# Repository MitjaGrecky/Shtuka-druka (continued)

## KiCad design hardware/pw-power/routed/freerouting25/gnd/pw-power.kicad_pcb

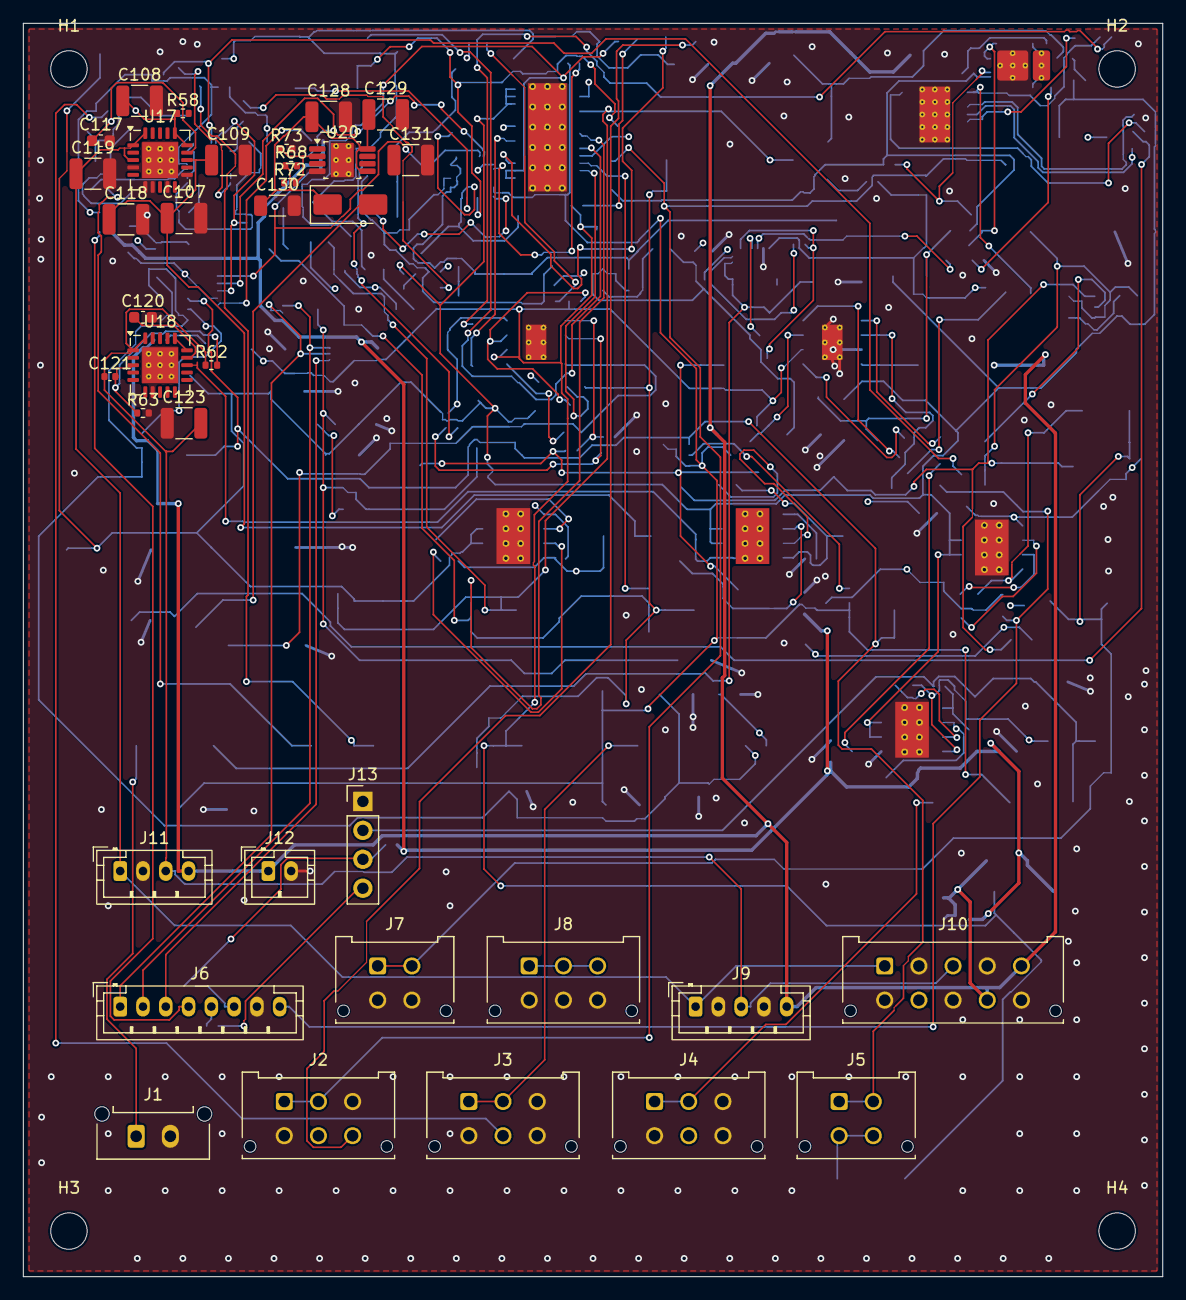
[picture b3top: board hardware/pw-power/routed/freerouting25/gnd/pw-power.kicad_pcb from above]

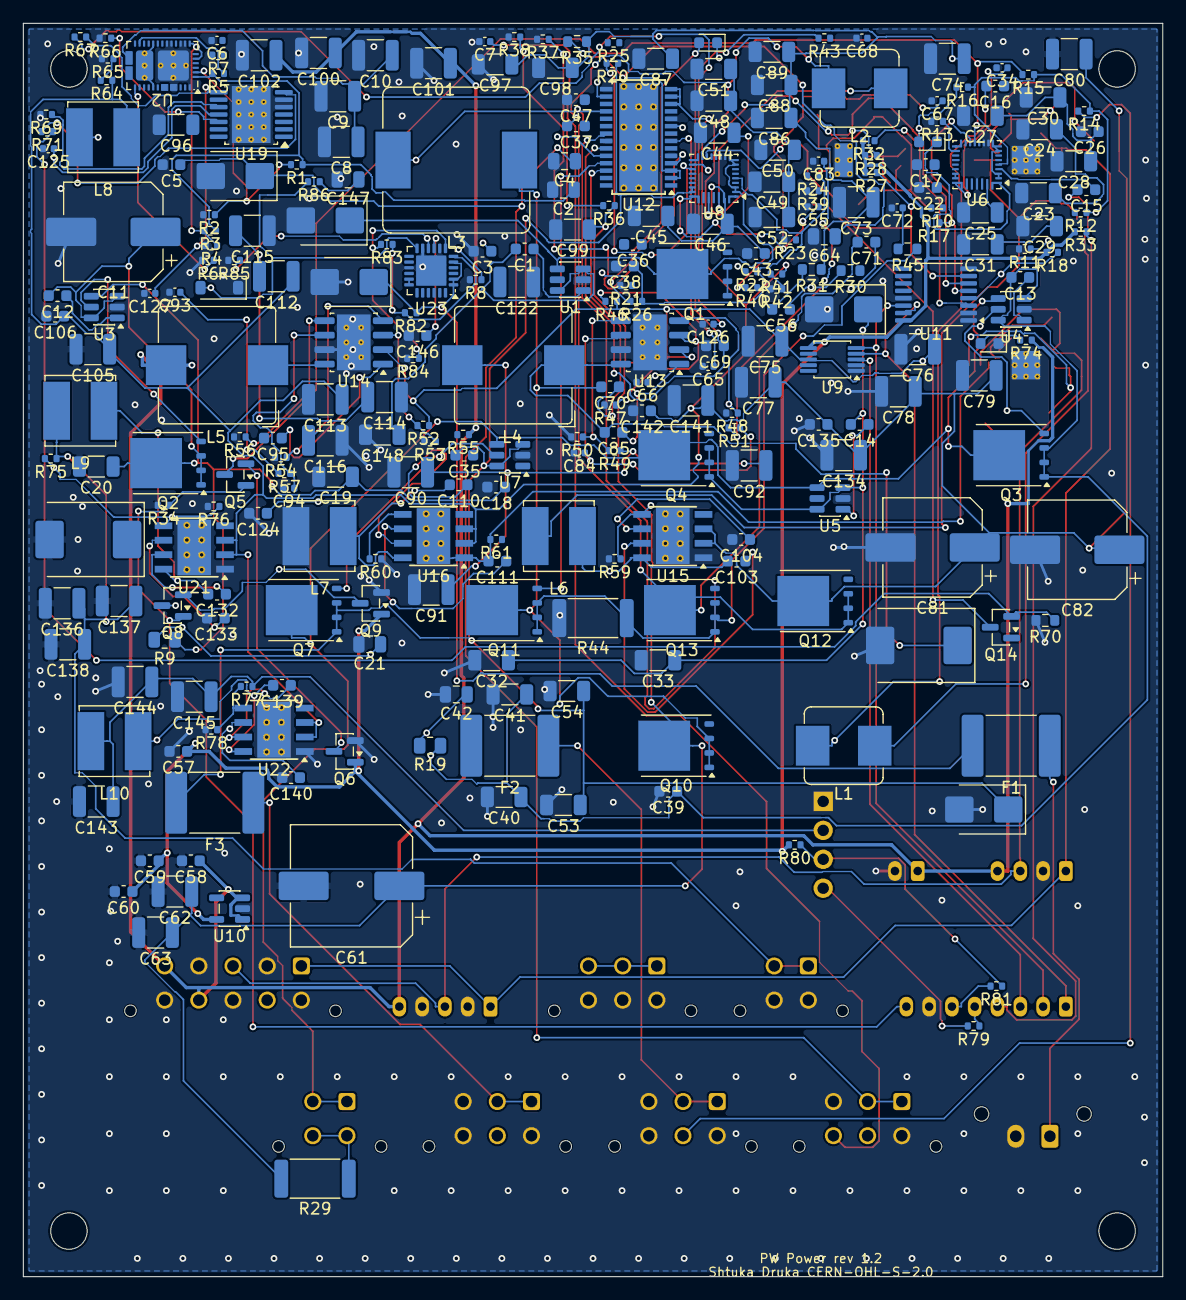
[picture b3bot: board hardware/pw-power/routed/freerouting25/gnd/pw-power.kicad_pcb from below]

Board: 4 copper layers, 100.0 x 110.0 mm, 313 parts (273 on the bottom side), 169 nets.

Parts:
C1, C12, C13, C14, C26, C35, C47, C85, C95, C103, C110, C132, C139: 100n 25V; C_0603_1608Metric
C2: 10u; C_0805_2012Metric
C3: 4.7u; C_0603_1608Metric
C4: 4.7u 25V; C_0805_2012Metric
C5, C146: 10n 50V; C_0603_1608Metric
C6, C7: 330p; C_0402_1005Metric
C8, C9, C107, C108, C109, C114, C115, C116, C136, C137, C138, C143, C144, C145: 22u 25V; C_1210_3225Metric
C10, C118, C119, C122: 10u 25V; C_1210_3225Metric
C11: 47u 35V; CP_Elec_8x10.5
C15, C16, C36, C37: 47n 25V; C_0603_1608Metric
C17, C38: 4.7u 10V; C_0603_1608Metric
C18, C22, C39, C43, C56, C70, C71: 100n 50V; C_0603_1608Metric
C19, C20, C23, C24, C25, C40, C41, C44, C45, C46, C148: 10u 35V; C_1206_3216Metric
C21, C42: 2.2u 35V; C_0805_2012Metric
C27, C28, C29, C30, C31, C32, C33, C48, C49, C50, C51, C52, C53, C54: 10u 25V; C_1206_3216Metric
C34, C55: 1n 50V; C_0402_1005Metric
C57, C60: 100n; C_0603_1608Metric
C58, C59, C104, C111, C117, C120, C133, C140: 1u; C_0603_1608Metric
C61: 100u 35V; CP_Elec_10x10.5
C62, C63, C105, C112, C113, C134, C141: 10u 50V; C_1210_3225Metric
C64, C147: 1u 50V; C_0805_2012Metric
C65: 220p; C_0402_1005Metric
C66: 100n; C_0402_1005Metric
C67: 33n; C_0402_1005Metric
C68: 560p; C_0402_1005Metric
C69, C124: 1u 25V; C_0603_1608Metric
C72, C84, C94: 47p; C_0402_1005Metric
C73, C74, C75, C76: 4.7u 50V; C_1210_3225Metric
C77, C78, C79, C80: 10u 35V; C_1210_3225Metric
C81, C82: 100u 35V; CP_Elec_8x10.5
C83, C93: 4.7n; C_0402_1005Metric
C86, C87, C88, C89, C96, C97, C98, C99: 2.2u 50V; C_1206_3216Metric
C90, C91, C92, C100, C101, C102: 47u 10V; C_1210_3225Metric
C106, C135, C142: 220n 50V; C_0603_1608Metric
C121: 10n; C_0402_1005Metric
C123: 47u 25V; C_1210_3225Metric
C125: 47n; C_0402_1005Metric
C126: 22n; C_0402_1005Metric
C127: 470p; C_0402_1005Metric
C128, C129, C131: 4.7u 100V; C_1210_3225Metric
C130: 1u 100V; C_1206_3216Metric
D1: SMBJ28CA; D_SMB
D2, D3: SMBJ20CA; D_SMB
D4, D6: SMBJ13CA; D_SMB
D5, D7, D11: green; LED_0603_1608Metric
D8, D9: B560C; D_SMC
D10: SS1H10; D_SMA
D12: BZT52C3V3; D_SOD-123
F1: 5A; Fuse_2920_7451Metric
F2, F3: 10A; Fuse_2920_7451Metric
H1, H2, H3, H4: M3; MountingHole_3.2mm_M3_ISO7380
J1: DC in; Molex_Micro-Fit_3.0_43650-0215_1x02_P3.00mm_Vertical
J2: USB-C Power in; Molex_Micro-Fit_3.0_43045-0612_2x03_P3.00mm_Vertical
J3: Battery 1; Molex_Micro-Fit_3.0_43045-0612_2x03_P3.00mm_Vertical
J4: Battery 2; Molex_Micro-Fit_3.0_43045-0612_2x03_P3.00mm_Vertical
J5: On/Off switch; Molex_Micro-Fit_3.0_43045-0412_2x02_P3.00mm_Vertical
J6: Power telemetry to P2; JST_PH_B8B-PH-K_1x08_P2.00mm_Vertical
J7: 15 V to H5; Molex_Micro-Fit_3.0_43045-0412_2x02_P3.00mm_Vertical
J8: +5V panel; Molex_Micro-Fit_3.0_43045-0612_2x03_P3.00mm_Vertical
J9: to R2; JST_PH_B5B-PH-K_1x05_P2.00mm_Vertical
J10: to A1/R1; Molex_Micro-Fit_3.0_43045-1012_2x05_P3.00mm_Vertical
J11: to F1; JST_PH_B4B-PH-K_1x04_P2.00mm_Vertical
J12: +5V screen; JST_PH_B2B-PH-K_1x02_P2.00mm_Vertical
J13: Fan 12 V PWM; PinHeader_1x04_P2.54mm_Vertical
L1, L2: 1uH; L_Bourns_SRP7028A_7.3x6.6mm
L3: 4.7uH; L_Bourns_SRP1245A
L4, L5: 8.2uH; L_Bourns_SRP1038C_10.0x10.0mm
L6, L7, L9, L10: 10uH; L_Bourns_SRN6045TA
L8: 22uH; L_Bourns_SRN6045TA
Q1, Q2, Q3, Q4, Q7, Q10, Q11, Q12, Q13: CSD18532Q5B; TDSON-8-1
Q5, Q6, Q8, Q9: 2N7002; SOT-23
Q14: IRLML0100; SOT-23
R1, R3: 42.2k; R_0402_1005Metric
R2, R4, R5, R6, R7, R8, R17, R18, R27, R28, R32, R33, R40, R43, R67, R69, R73, R80: 10k; R_0402_1005Metric
R9, R19: 2; R_0805_2012Metric
R10, R20, R71, R79, R81: 100; R_0402_1005Metric
R11, R21: 10.5k; R_0402_1005Metric
R12, R22: 47k; R_0402_1005Metric
R13, R15, R23, R25, R34, R58, R60, R64, R75, R77: 100k; R_0402_1005Metric
R14, R24: 9.31k; R_0402_1005Metric
R16, R26, R74: 2.2k; R_0402_1005Metric
R29: 5m; R_2512_6332Metric
R30, R31, R35: 10; R_0603_1608Metric
R36: 249k; R_0402_1005Metric
R37: 32.4k; R_0402_1005Metric
R38: 93.1k; R_0402_1005Metric
R39: 27.4k; R_0402_1005Metric
R41, R82: 453k; R_0402_1005Metric
R42: 20k; R_0402_1005Metric
R44: 8m; R_2512_6332Metric
R45: 100; R_0603_1608Metric
R46, R52: 442k; R_0402_1005Metric
R47, R53: 90.9k; R_0402_1005Metric
R48, R54: 243k; R_0402_1005Metric
R49, R55: 53.6k; R_0402_1005Metric
R50, R56: 10.2k; R_0402_1005Metric
R51, R57: 16.9k; R_0402_1005Metric
R59, R61: 7.68k; R_0402_1005Metric
R62: 102k; R_0402_1005Metric
R63: 11k; R_0402_1005Metric
R65, R84: 27k; R_0402_1005Metric
R66: 49.9k; R_0402_1005Metric
R68: 475k; R_0402_1005Metric
R70: 0.1; R_0603_1608Metric
R72: 383k; R_0402_1005Metric
R76: 7.15k; R_0402_1005Metric
R78: 9.09k; R_0402_1005Metric
R83: 35.7k; R_0402_1005Metric
R85: 3.32k; R_0402_1005Metric
R86: 220k; R_0402_1005Metric
U1, U3, U4, U5, U7: LM74700-Q1; SOT-23-6
U2: TPS25730D; Texas_REF0038A_WQFN-38-2EP_6x4mm_P0.4
U6, U8: BQ25798; Texas_RQM0029A_VQFN-29_4x4mm_P0.4mm
U9: INA226; MSOP-10_3x3mm_P0.5mm
U10: AP2112K-3.3; SOT-23-5
U11: TCA9546APW; TSSOP-16_4.4x5mm_P0.65mm
U12: LM5176; HTSSOP-28-1EP_4.4x9.7mm_P0.65mm_EP3.4x9.5mm_ThermalVias
U13, U14: TPS54560B; Texas_R-PDSO-G8_EP2.95x4.9mm_Mask2.4x3.1mm_ThermalVias
U15, U16, U21, U22: LMR33640; Texas_HSOP-8-1EP_3.9x4.9mm_P1.27mm_ThermalVias
U17: TPS7A4701; Texas_RGW0020A_VQFN-20-1EP_5x5mm_P0.65mm_EP3.15x3.15mm_Ther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
U18: TPS7A3301; Texas_RGW0020A_VQFN-20-1EP_5x5mm_P0.65mm_EP3.15x3.15mm_Ther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
U19: LM5156H; Texas_HTSSOP-14-1EP_4.4x5mm_P0.65mm_EP3.4x5mm_Mask3.155x3.2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
U20: TPS7A4101; Texas_DGN0008B_VSSOP-8-1EP_3x3mm_P0.65mm_EP2x3mm_Mask1.88x1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
U23: TPS26631RGER; QFN-24-1EP_4x4mm_P0.5mm_EP2.65x2.65mm

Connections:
+3V3: C57.1, C59.1, C60.1, Q6.1, Q9.1, R17.2, R18.2, R27.2, R28.2, R32.2, R33.2, R80.2, U9.6, U10.5, U11.16
+5V: C58.1, C100.1, C101.1, C102.1, J9.5, J10.5, J10.9, J11.4, J12.1, L5.2, R55.1, R74.1, U10.1, U10.3
/+5V_PANEL: C90.1, C91.1, C92.1, J8.1, J8.2, J8.3, L4.2, R49.1
/+12V: C119.1, J9.1, J10.1, J11.1, U17.1, U17.3, U17.20
/+48V: C131.1, J10.7, R72.1, U20.1
/-12V: C121.1, C123.2, J9.3, J10.3, J11.3, R62.1, U18.1, U18.20
/B19_BOOT1: C70.1, U12.26
/B19_BOOT2: C71.1, U12.20
/B19_CMP_RC: C67.1, R40.2
/B19_COMP: C68.1, R40.1, U12.9
/B19_CS: C72.1, R45.2, U12.16
/B19_CSN: Q11.1, Q11.2, Q11.3, Q13.1, Q13.2, Q13.3, R44.1, R45.1
/B19_FB: R41.2, R42.1, U12.11
/B19_HDRV1: Q10.4, U12.27
/B19_HDRV2: Q12.4, U12.19
/B19_LDRV1: Q11.4, U12.25
/B19_LDRV2: Q13.4, U12.21
/B19_MODE: R38.1, U12.4
/B19_PG: R43.1, U12.17
/B19_RT: R39.1, U12.6
/B19_SLOPE: C65.1, U12.7
/B19_SS: C66.1, U12.8
/B19_SW1: C70.2, L3.1, Q10.1, Q10.2, Q10.3, Q11.5, U12.28
/B19_SW2: C71.2, L3.2, Q12.1, Q12.2, Q12.3, Q13.5, U12.18
/B19_UVLO: R36.2, R37.1, U12.1
/B19_VCC: C69.1, R43.2, U12.23
/B19_VIN: C64.1, R35.2, U12.2, U12.3
/BAT1_F: C14.2, C32.1, C33.1, D4.1, F2.2, Q4.1, Q4.2, Q4.3, R10.1, U5.3, U5.6, U6.22, U6.23
/BAT1_RAW: F2.1, J3.1, J3.2
/BAT2_F: C35.2, C53.1, C54.1, D6.1, F3.2, Q7.1, Q7.2, Q7.3, R20.1, U7.3, U7.6, U8.22, U8.23
/BAT2_RAW: F3.1, J4.1, J4.2
/BUS: C61.1, C62.1, C63.1, C73.1, C74.1, C75.1, C76.1, C86.1, C87.1, C88.1, C89.1, C96.1, C97.1, C98.1, C99.1, Q10.5, R29.2, R31.1, R35.1, R36.1, R46.1, R52.1, U9.8, U13.2, U14.2
/BUS_IN: J5.1, J5.2, Q3.5, Q4.5, Q7.5, U4.4, U5.4, U7.4
/BUS_SW: J5.3, J5.4, R29.1, R30.1
/CH1_BATP: R10.2, U6.18
/CH1_BTST1: C15.1, U6.4
/CH1_BTST2: C16.1, U6.19
/CH1_CE: Q5.3, R15.2, U6.13
/CH1_CEM: Q5.2, Q6.3
/CH1_ILIM: R12.2, R13.1, U6.17
/CH1_LEDA: D5.2, R16.2
/CH1_PMID: C22.1, C23.1, C24.1, C25.1, U6.29
/CH1_PROG: R11.1, U6.20
/CH1_REGN: C17.1, R12.1, R14.1, R15.1, R16.1, U6.5
/CH1_SCL: R17.1, U6.14, U11.5
/CH1_SDA: R18.1, U6.15, U11.4
/CH1_SDRV: C34.1, U6.24
/CH1_SNUB: C21.1, R9.2
/CH1_STAT: D5.1, U6.1
/CH1_SW1: C15.2, L1.1, U6.28
/CH1_SW2: C16.2, L1.2, U6.26
/CH1_SYS: C26.1, C27.1, C28.1, C29.1, C30.1, C31.1, U6.25
/CH1_TS: J3.5, R14.2, U6.16
/CH2_BATP: R20.2, U8.18
/CH2_BTST1: C36.1, U8.4
/CH2_BTST2: C37.1, U8.19
/CH2_CE: Q8.3, R25.2, U8.13
/CH2_CEM: Q8.2, Q9.3
/CH2_ILIM: R22.2, R23.1, U8.17
/CH2_LEDA: D7.2, R26.2
/CH2_PMID: C43.1, C44.1, C45.1, C46.1, U8.29
/CH2_PROG: R21.1, U8.20
/CH2_REGN: C38.1, R22.1, R24.1, R25.1, R26.1, U8.5
/CH2_SCL: R27.1, U8.14, U11.7
/CH2_SDA: R28.1, U8.15, U11.6
/CH2_SDRV: C55.1, U8.24
/CH2_SNUB: C42.1, R19.2
/CH2_STAT: D7.1, U8.1
/CH2_SW1: C36.2, L2.1, U8.28
/CH2_SW2: C37.2, L2.2, U8.26
/CH2_SYS: C47.1, C48.1, C49.1, C50.1, C51.1, C52.1, U8.25
/CH2_TS: J4.5, R24.2, U8.16
/CHG_EN: J6.8, Q5.1, Q8.1, R34.1
/CHG_INT: J6.4, R33.1, U6.21, U8.21
/DC_F: C147.1, D1.1, F1.2, R82.1, R86.1, U23.1, U23.2, U23.5
/DC_P: C1.2, C148.1, Q1.1, Q1.2, Q1.3, U1.3, U1.6, U23.17, U23.18
/DC_RAW: F1.1, J1.1
/EF_DVDT: C146.1, U23.9
/EF_ILIM: R85.1, U23.10
/EF_OV: R83.2, R84.1, U23.7
/EF_SHDN: D12.2, R86.2, U23.12
/EF_UV: R82.2, R83.1, U23.6
/EXT: C13.2, C18.1, C19.1, C20.1, C39.1, C40.1, C41.1, D3.1, Q1.5, Q2.5, Q3.1, Q3.2, Q3.3, R9.1, R19.1, U1.4, U3.4, U4.3, U4.6, U6.2, U6.3, U6.8, U6.9, U8.2, U8.3, U8.8, U8.9
/FAN_PWM: J13.4, R79.2
/FAN_PWM_IN: J6.5, R79.1
/FAN_TACH: J13.3, R80.1, R81.1
/FAN_TACH_OUT: J6.6, R81.2
/HV_COMP: C127.1, R67.1, U19.8
/HV_CRC: C126.1, R67.2
/HV_CS: R71.2, U19.7
/HV_CSN: Q14.2, R70.1, R71.1
/HV_FB: R68.2, R69.1, U19.10
/HV_GATE: Q14.1, U19.4
/HV_RAW: C128.1, C129.1, C130.1, D10.1, R68.1, U20.5, U20.8
/HV_RT: R66.1, U19.12
/HV_SS: C125.1, U19.11
/HV_SW: D10.2, L8.2, Q14.3
/HV_UVLO: R64.2, R65.1, U19.14
/HV_VCC: C124.1, U19.3, U19.9
/IBAT1_GATE: Q4.4, U5.5
/IBAT1_VCAP: C14.1, U5.1
/IBAT2_GATE: Q7.4, U7.5
/IBAT2_VCAP: C35.1, U7.1
/IDC_GATE: Q1.4, U1.5
/IDC_VCAP: C1.1, U1.1
/IEXT_GATE: Q3.4, U4.5
/IEXT_VCAP: C13.1, U4.1
/IPD_GATE: Q2.4, U3.5
/IPD_VCAP: C12.1, U3.1
/LED_K: D11.2, R74.2
/MUX_RST: R32.1, U11.3
/N12_FB: C121.2, R62.2, R63.1, U18.3
/N12_NR: C120.1, U18.14
/N14: C111.2, C112.2, C114.2, C115.2, C116.2, C122.2, R61.2, U16.1, U16.9, U18.13, U18.15, U18.16
/N14_BOOT: C110.1, U16.7
/N14_FB: R60.2, R61.1, U16.5
/N14_SW: C110.2, L7.1, U16.8
/N14_VCC: C111.1, U16.6
/P5VPANEL_BOOT: C85.1, U13.1
/P5VPANEL_COMP: C84.1, R51.1, U13.6
/P5VPANEL_CRC: C83.1, R51.2
/P5VPANEL_EN: R46.2, R47.1, U13.3
/P5VPANEL_FB: R49.2, R50.1, U13.5
/P5VPANEL_RT: R48.1, U13.4
/P5VPANEL_SW: C85.2, D8.1, L4.1, U13.8
/P5V_BOOT: C95.1, U14.1
/P5V_COMP: C94.1, R57.1, U14.6
/P5V_CRC: C93.1, R57.2
/P5V_EN: R52.2, R53.1, U14.3
/P5V_FB: R55.2, R56.1, U14.5
/P5V_RT: R54.1, U14.4
/P5V_SW: C95.2, D9.1, L5.1, U14.8
/P12_NR: C117.1, U17.14
/P14: C107.1, C108.1, C109.1, C118.1, L6.2, R58.1, U17.13, U17.15, U17.16
/P14_BOOT: C103.1, U15.7
/P14_FB: R58.2, R59.1, U15.5
/P14_SW: C103.2, L6.1, U15.8
/P14_VCC: C104.1, U15.6
/P48_FB: R72.2, R73.1, U20.2
/PD_ADCIN1: R1.2, R2.1, U2.2
/PD_ADCIN34: R3.2, R4.1, U2.5, U2.7
/PD_CC1: C6.1, J2.5, U2.28
/PD_CC2: C7.1, J2.6, U2.29
/PD_DRAIN: U2.15, U2.30, U2.40
/PD_FAULT: R5.1, U2.18
/PD_LDO1V5: C3.1, U2.4
/PD_LDO3V3: C2.1, R1.1, R3.1, R5.2, U2.1, U2.3
/PD_OUT: C8.1, C9.1, C10.1, C11.1, C12.2, Q2.1, Q2.2, Q2.3, U2.20, U3.3, U3.6
/PD_RSV26: R6.1, U2.26
/PD_RSV27: R7.1, U2.27
/PD_RSV36: R8.1, U2.36
/PD_VBUS: C4.1, C5.1, D2.1, J2.1, J2.2, U2.23, U2.32
/PM_ALERT: J6.3, U9.3
/PM_INN: C56.2, R31.2, U9.9
/PM_INP: C56.1, R30.2, U9.10
/PM_SCL: J6.2, U9.5, U11.14
/PM_SDA: J6.1, U9.4, U11.15
/V12F: C143.1, C144.1, C145.1, J13.2, L10.2, R77.1
/V12F_BOOT: C139.1, U22.7
/V12F_FB: R77.2, R78.1, U22.5
/V12F_SW: C139.2, L10.1, U22.8
/V12F_VCC: C140.1, U22.6
/V15: C136.1, C137.1, C138.1, J7.1, J7.2, L9.2, R75.1
/V15_BOOT: C132.1, U21.7
/V15_FB: R75.2, R76.1, U21.5
/V15_SW: C132.2, L9.1, U21.8
/V15_VCC: C133.1, U21.6
/V19: C77.1, C78.1, C79.1, C80.1, C81.1, C82.1, C105.1, C106.1, C112.1, C113.1, C134.1, C135.1, C141.1, C142.1, L8.1, Q12.5, R41.1, R64.1, U12.12, U12.13, U12.14, U12.24, U15.2, U15.3, U16.2, U16.3, U19.1, U21.2, U21.3, U22.2, U22.3
GND: C2.2, C3.2, C4.2, C5.2, C6.2, C7.2, C8.2, C9.2, C10.2, C11.2, C17.2, C18.2, C19.2, C20.2, C21.2, C22.2, C23.2, C24.2, C25.2, C26.2, C27.2, C28.2, C29.2, C30.2, C31.2, C32.2, C33.2, C34.2, C38.2, C39.2, C40.2, C41.2, C42.2, C43.2, C44.2, C45.2, C46.2, C47.2, C48.2, C49.2, C50.2, C51.2, C52.2, C53.2, C54.2, C55.2, C57.2, C58.2, C59.2, C60.2, C61.2, C62.2, C63.2, C64.2, C65.2, C66.2, C67.2, C68.2, C69.2, C72.2, C73.2, C74.2, C75.2, C76.2, C77.2, C78.2, C79.2, C80.2, C81.2, C82.2, C83.2, C84.2, C86.2, C87.2, C88.2, C89.2, C90.2, C91.2, C92.2, C93.2, C94.2, C96.2, C97.2, C98.2, C99.2, C100.2, C101.2, C102.2, C104.2, C105.2, C106.2, C107.2, C108.2, C109.2, C113.2, C114.1, C115.1, C116.1, C117.2, C118.2, C119.2, C120.2, C122.1, C123.1, C124.2, C125.2, C126.2, C127.2, C128.2, C129.2, C130.2, C131.2, C133.2, C134.2, C135.2, C136.2, C137.2, C138.2, C140.2, C141.2, C142.2, C143.2, C144.2, C145.2, C146.2, C147.2, C148.2, D1.2, D2.2, D3.2, D4.2, D6.2, D8.2, D9.2, D11.1, D12.1, J1.2, J2.3, J2.4, J3.3, J3.4, J3.6, J4.3, J4.4, J4.6, J6.7, J7.3, J7.4, J8.4, J8.5, J8.6, J9.2, J9.4, J10.2, J10.4, J10.6, J10.8, J10.10, J11.2, J12.2, J13.1, L7.2, Q6.2, Q9.2, R2.2, R4.2, R6.2, R7.2, R8.2, R11.2, R13.2, R21.2, R23.2, R34.2, R37.2, R38.2, R39.2, R42.2, R44.2, R47.2, R48.2, R50.2, R53.2, R54.2, R56.2, R59.2, R60.1, R63.2, R65.2, R66.2, R69.2, R70.2, R73.2, R76.2, R78.2, R84.2, R85.2, U1.2, U2.8, U2.9, U2.11, U2.12, U2.14, U2.16, U2.17, U2.31, U2.34, U2.38, U2.39, U3.2, U4.2, U5.2, U6.10, U6.11, U6.27, U7.2, U8.10, U8.11, U8.27, U9.1, U9.2, U9.7, U10.2, U11.1, U11.2, U11.8, U11.13, U12.5, U12.10, U12.15, U12.22, U12.29, U13.7, U13.9, U14.7, U14.9, U15.1, U15.9, U17.4, U17.6, U17.7, U17.9, U17.11, U17.21, U18.7, U18.21, U19.5, U19.6, U19.15, U20.4, U20.9, U21.1, U21.9, U22.1, U22.9, U23.8, U23.11, U23.15, U23.25
